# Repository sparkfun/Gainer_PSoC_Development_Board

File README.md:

SparkFun Gainer PSoC Development Board
========================================

[*SparkFun Gainer PSoC Development Board (DEV-08480)*](https://www.sparkfun.com/products/8480)

This board utilizes the Cypress PSoC CY8C29466 IC making it a great board for digital and analog projects where AtoD and DtoA is required.
 Simple USB interface for reprogramming - no external programmer needed.

Repository Contents
-------------------
* **/Hardware** - All Eagle design files (.brd, .sch)

License Information
-------------------
The hardware is released under [Creative Commons ShareAlike 4.0 International](https://creativecommons.org/licenses/by-sa/4.0/).

Gainer is a simple board developed by Shigeru Kobayashi and the team at Gainer.cc. 

Distributed as-is; no warranty is given.

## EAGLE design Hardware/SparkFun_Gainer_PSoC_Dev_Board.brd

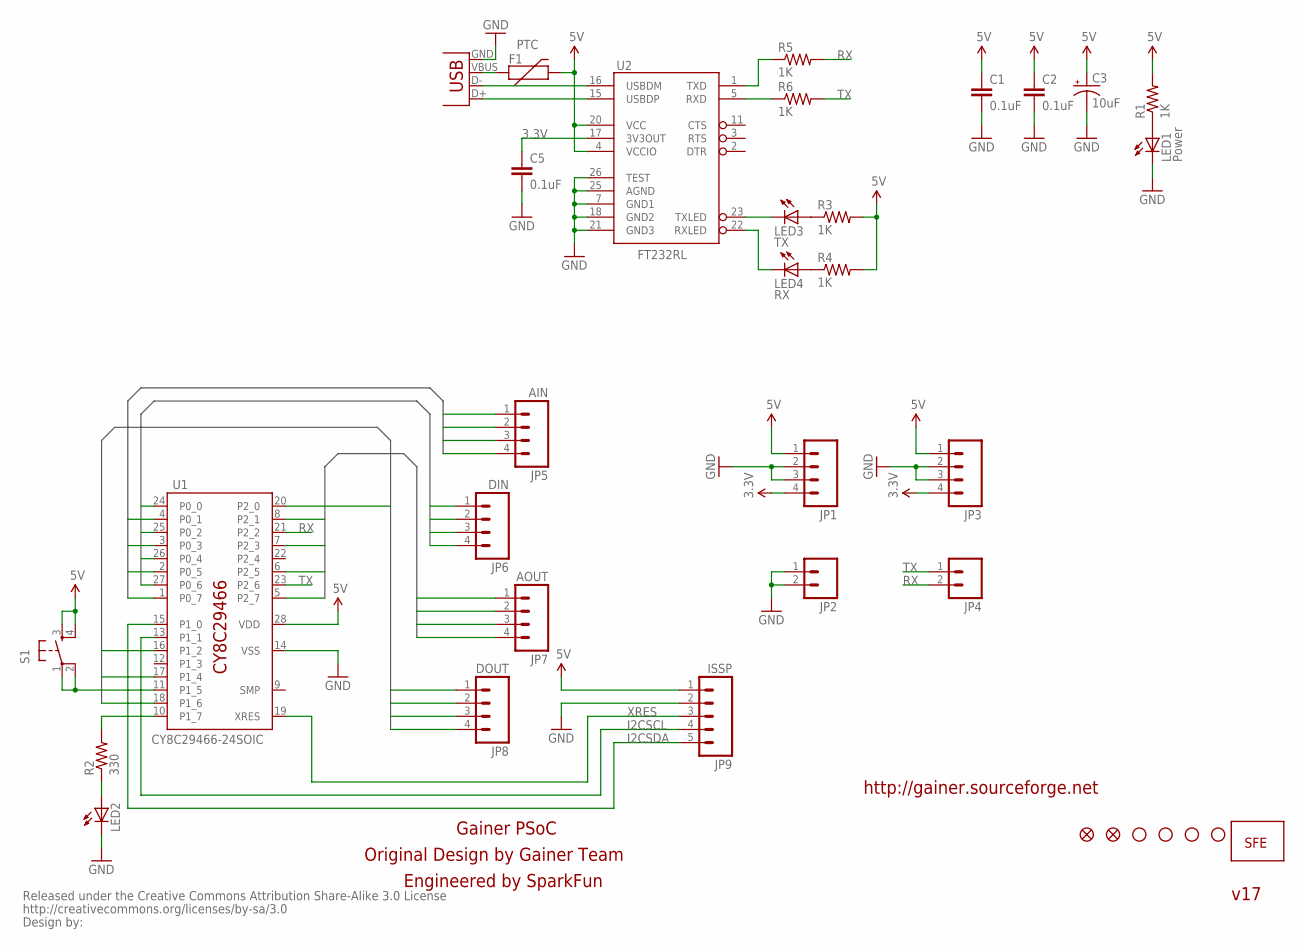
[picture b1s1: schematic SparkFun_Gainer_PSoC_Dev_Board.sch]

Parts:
C1, C2, C5: 0.1uF; C0402
C3: 10uF; EIA3216
F1: PTC; PTC-1206
JP1, JP3: M04PTH; 1X04
JP2, JP4: M02PTH; 1X02
JP5: AIN; 1X04
JP6: DIN; 1X04
JP7: AOUT; 1X04
JP8: DOUT; 1X04
JP9: ISSP; 1X05
LED1: Power; LED-1206
LED2: LED1206; LED-1206
LED3: TX; LED-0603
LED4: RX; LED-0603
R1, R3, R4, R5, R6: 1K; C0402
R2: 330; C0402
S1: TAC_SWITCHSMD; TACTILE_SWITCH_SMD
U1: CY8C29466-24SOIC; SOIC28
U2: FT232RL; SSOP28DB
U$1: LOGO-SFENEW; SFE-NEW-WEBLOGO
U$10, U$17: FIDUCIAL1X2; FIDUCIAL-1X2
U$12, U$13, U$14, U$15: STAND-OFF
U$18: CREATIVE_COMMONS
X2: USBSMD; USB-MINIB

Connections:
3.3V: C5.1, JP1.4, JP3.4, U2.17 (3V3OUT)
5V: C1.1, C2.1, C3.A (+), F1.2, JP1.1, JP3.1, JP9.1, R1.2, R3.2, R4.2, S1.3, S1.4, U1.28 (VDD), U2.4 (VCCIO), U2.20 (VCC)
AIN1: JP5.1, U1.1 (P0_7)
AIN2: JP5.2, U1.2 (P0_5)
AIN3: JP5.3, U1.3 (P0_3)
AIN4: JP5.4, U1.4 (P0_1)
AOUT1: JP7.1, U1.5 (P2_7)
AOUT2: JP7.2, U1.6 (P2_5)
AOUT3: JP7.3, U1.7 (P2_3)
AOUT4: JP7.4, U1.8 (P2_1)
DIN1: JP6.1, U1.27 (P0_6)
DIN2: JP6.2, U1.26 (P0_4)
DIN3: JP6.3, U1.25 (P0_2)
DIN4: JP6.4, U1.24 (P0_0)
DOUT1: JP8.1, U1.20 (P2_0)
DOUT2: JP8.2, U1.18 (P1_6)
DOUT3: JP8.3, U1.17 (P1_4)
DOUT4: JP8.4, U1.16 (P1_2)
GND: C1.2, C2.2, C3.C (-), C5.2, JP1.2, JP1.3, JP2.1, JP2.2, JP3.2, JP3.3, JP9.2, LED1.C, LED2.C, U1.14 (VSS), U2.7 (GND1), U2.18 (GND2), U2.21 (GND3), U2.25 (AGND), U2.26 (TEST), X2.GND
I2CSCL: JP9.4, U1.13 (P1_1)
I2CSDA: JP9.5, U1.15 (P1_0)
unnamed: LED3.A, R3.1
unnamed: F1.1, X2.VBUS
unnamed: LED1.A, R1.1
unnamed: LED4.A, R4.1
unnamed: R6.1, U2.5 (RXD)
unnamed: LED4.C, U2.22 (RXLED)
unnamed: S1.1, S1.2, U1.11 (P1_5)
unnamed: R2.2, U1.10 (P1_7)
unnamed: LED2.A, R2.1
unnamed: U2.16 (USBDM), X2.D-
unnamed: U2.15 (USBDP), X2.D+
unnamed: R5.1, U2.1 (TXD)
unnamed: LED3.C, U2.23 (TXLED)
RX: JP4.2, R5.2, U1.21 (P2_2)
TX: JP4.1, R6.2, U1.23 (P2_6)
XRES: JP9.3, U1.19 (XRES)

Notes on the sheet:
Gainer PSoC
http://gainer.sourceforge.net
Original Design by Gainer Team
Engineered by SparkFun
v17

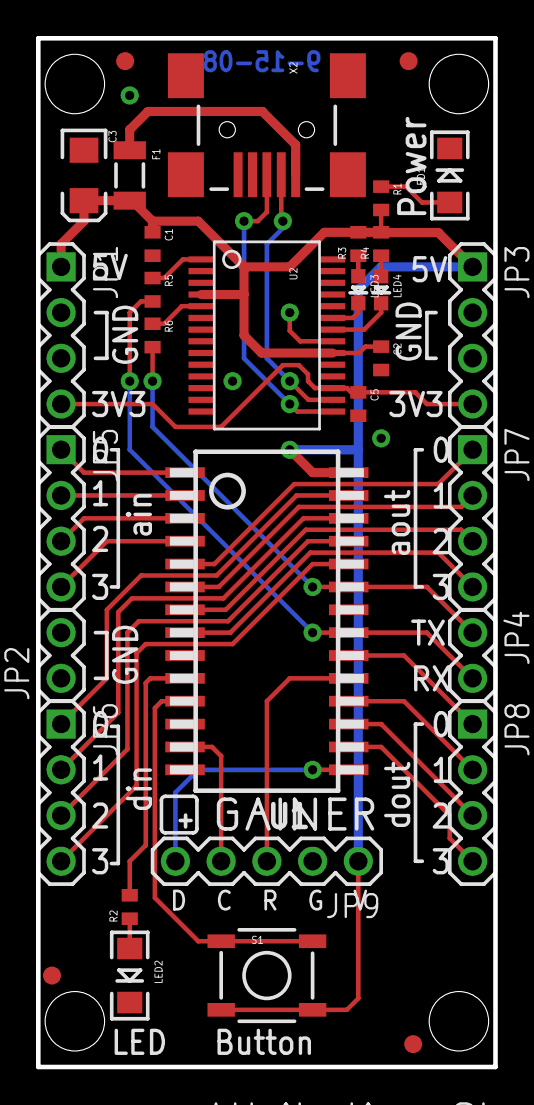
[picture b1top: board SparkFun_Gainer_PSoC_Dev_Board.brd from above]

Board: 2 copper layers, 25.4 x 57.1 mm, 39 parts (1 on the bottom side), 37 nets.

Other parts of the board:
E$1, E$2: FIDUCIAL-1X2
U$19: GAINER_LOGO

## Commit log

2015-01-29 Initial hardware commit

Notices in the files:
parts and their libraries:
SparkFun: Released under the Creative Commons Attribution Share-Alike 3.0 License
SparkFun: http://creativecommons.org/licenses/by-sa/3.0
